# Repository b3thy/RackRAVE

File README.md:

PCB & RaspberryPi image  
for RACKRAVE  
paper(Japanese):  
https://data.jssa.info/paper/2024v16n01/53_5.Kumon.pdf  
Modular synthesizer using realtime audio variational autoencoder  
RAVE:  
https://github.com/acids-ircam/RAVE

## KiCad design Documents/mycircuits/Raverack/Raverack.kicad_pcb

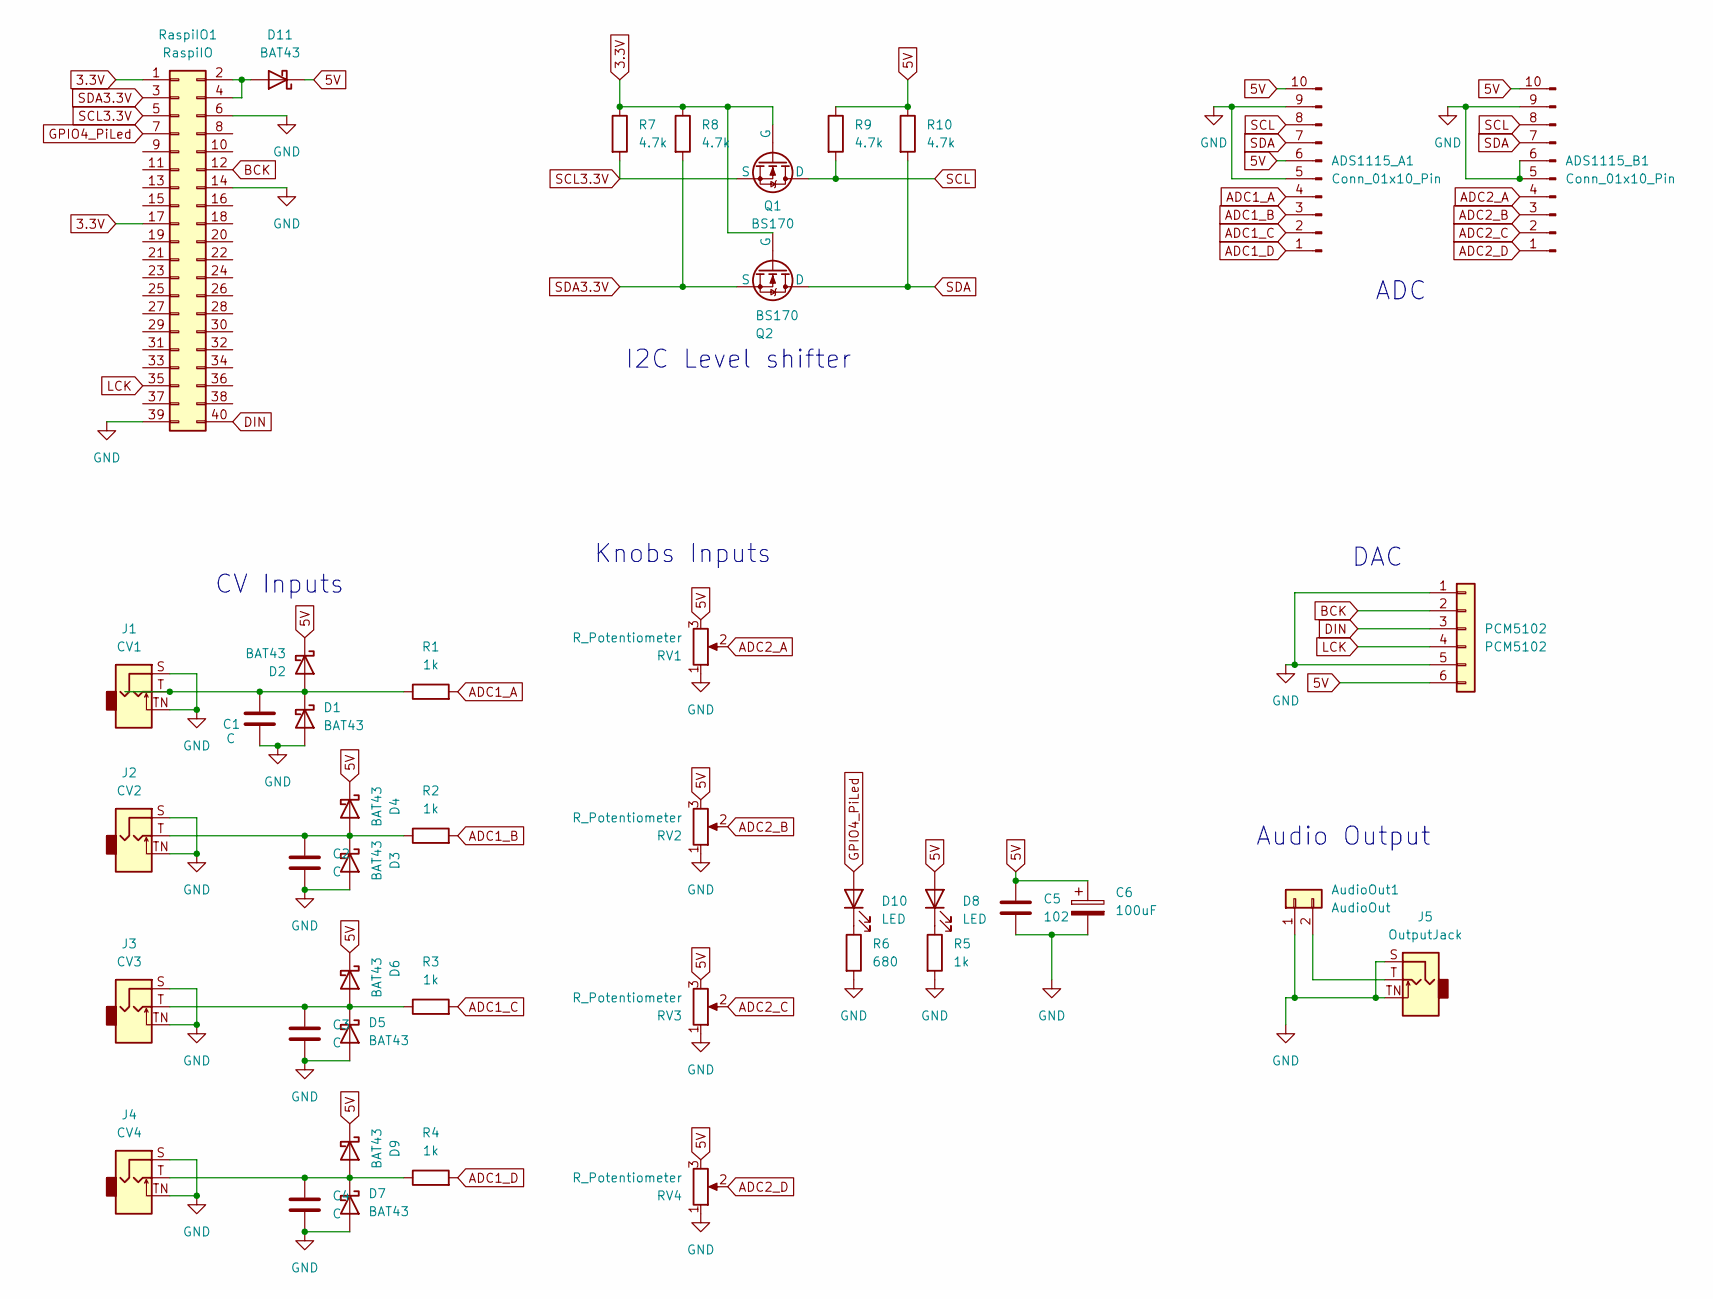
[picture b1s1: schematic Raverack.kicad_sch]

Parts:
ADS1115_A1, ADS1115_B1: Conn_01x10_Pin; PinHeader_1x10_P2.54mm_Vertical
AudioOut1: AudioOut; PinHeader_1x02_P2.54mm_Vertical
C1, C2, C3, C4: C; C_Disc_D3.8mm_W2.6mm_P2.50mm
C5: 102; C_Disc_D3.8mm_W2.6mm_P2.50mm
C6: 100uF; CP_Radial_D5.0mm_P2.50mm
D1, D2, D3, D4, D5, D6, D7, D9, D11: BAT43; D_DO-35_SOD27_P7.62mm_Horizontal
D8, D10: LED; LED_D3.0mm
J1: CV1; Jack_3.5mm_QingPu_WQP-PJ398SM_Vertical_CircularHoles
J2: CV2; Jack_3.5mm_QingPu_WQP-PJ398SM_Vertical_CircularHoles
J3: CV3; Jack_3.5mm_QingPu_WQP-PJ398SM_Vertical_CircularHoles
J4: CV4; Jack_3.5mm_QingPu_WQP-PJ398SM_Vertical_CircularHoles
J5: OutputJack; Jack_3.5mm_QingPu_WQP-PJ398SM_Vertical_CircularHoles
PCM5102: PCM5102; PinHeader_1x06_P2.54mm_Vertical
Q1, Q2: BS170; TO-92_Inline_Wide
R1, R2, R3, R4, R5: 1k; R_Axial_DIN0204_L3.6mm_D1.6mm_P5.08mm_Horizontal
R6: 680; R_Axial_DIN0204_L3.6mm_D1.6mm_P5.08mm_Horizontal
R7, R8, R9, R10: 4.7k; R_Axial_DIN0204_L3.6mm_D1.6mm_P5.08mm_Horizontal
RV1, RV2, RV3, RV4: R_Potentiometer; Potentiometer_Alps_RK09K_Single_Vertical
RaspiIO1: RaspiIO; PinHeader_2x20_P2.54mm_Vertical

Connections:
3.3V: Q1.2 (G), Q2.2 (G), R7.1, R8.1, RaspiIO1.1, RaspiIO1.17
5V: ADS1115_A1.6, ADS1115_A1.10, ADS1115_B1.10, C5.1, C6.1, D2.1 (K), D4.1 (K), D6.1 (K), D8.2 (A), D9.1 (K), D11.1 (K), PCM5102.6, R9.1, R10.1, RV1.3, RV2.3, RV3.3, RV4.3
ADC1_A: ADS1115_A1.4, R1.2
ADC1_B: ADS1115_A1.3, R2.2
ADC1_C: ADS1115_A1.2, R3.2
ADC1_D: ADS1115_A1.1, R4.2
ADC2_A: ADS1115_B1.4, RV1.2
ADC2_B: ADS1115_B1.3, RV2.2
ADC2_C: ADS1115_B1.2, RV3.2
ADC2_D: ADS1115_B1.1, RV4.2
BCK: PCM5102.2, RaspiIO1.12
DIN: PCM5102.3, RaspiIO1.40
GND: ADS1115_A1.5, ADS1115_A1.9, ADS1115_B1.5, ADS1115_B1.6, ADS1115_B1.9, AudioOut1.1, C1.2, C2.2, C3.2, C4.2, C5.2, C6.2, D1.2 (A), D3.2 (A), D5.2 (A), D7.2 (A), J1.S, J1.TN, J2.S, J2.TN, J3.S, J3.TN, J4.S, J4.TN, J5.S, J5.TN, PCM5102.1, PCM5102.5, R5.2, R6.2, RV1.1, RV2.1, RV3.1, RV4.1, RaspiIO1.6, RaspiIO1.14, RaspiIO1.39
GPIO4_PiLed: D10.2 (A), RaspiIO1.7
LCK: PCM5102.4, RaspiIO1.35
unnamed: AudioOut1.2, J5.T
unnamed: C1.1, D1.1 (K), D2.2 (A), J1.T, R1.1
unnamed: C2.1, D3.1 (K), D4.2 (A), J2.T, R2.1
unnamed: C3.1, D5.1 (K), D6.2 (A), J3.T, R3.1
unnamed: C4.1, D7.1 (K), D9.2 (A), J4.T, R4.1
unnamed: D8.1 (K), R5.1
unnamed: D10.1 (K), R6.1
unnamed: D11.2 (A), RaspiIO1.2, RaspiIO1.4
SCL: ADS1115_A1.8, ADS1115_B1.8, Q1.1 (D), R9.2
SCL3.3V: Q1.3 (S), R7.2, RaspiIO1.5
SDA: ADS1115_A1.7, ADS1115_B1.7, Q2.1 (D), R10.2
SDA3.3V: Q2.3 (S), R8.2, RaspiIO1.3

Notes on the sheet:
I2C Level shifter
Knobs Inputs
CV Inputs
ADC
Audio Output
DAC

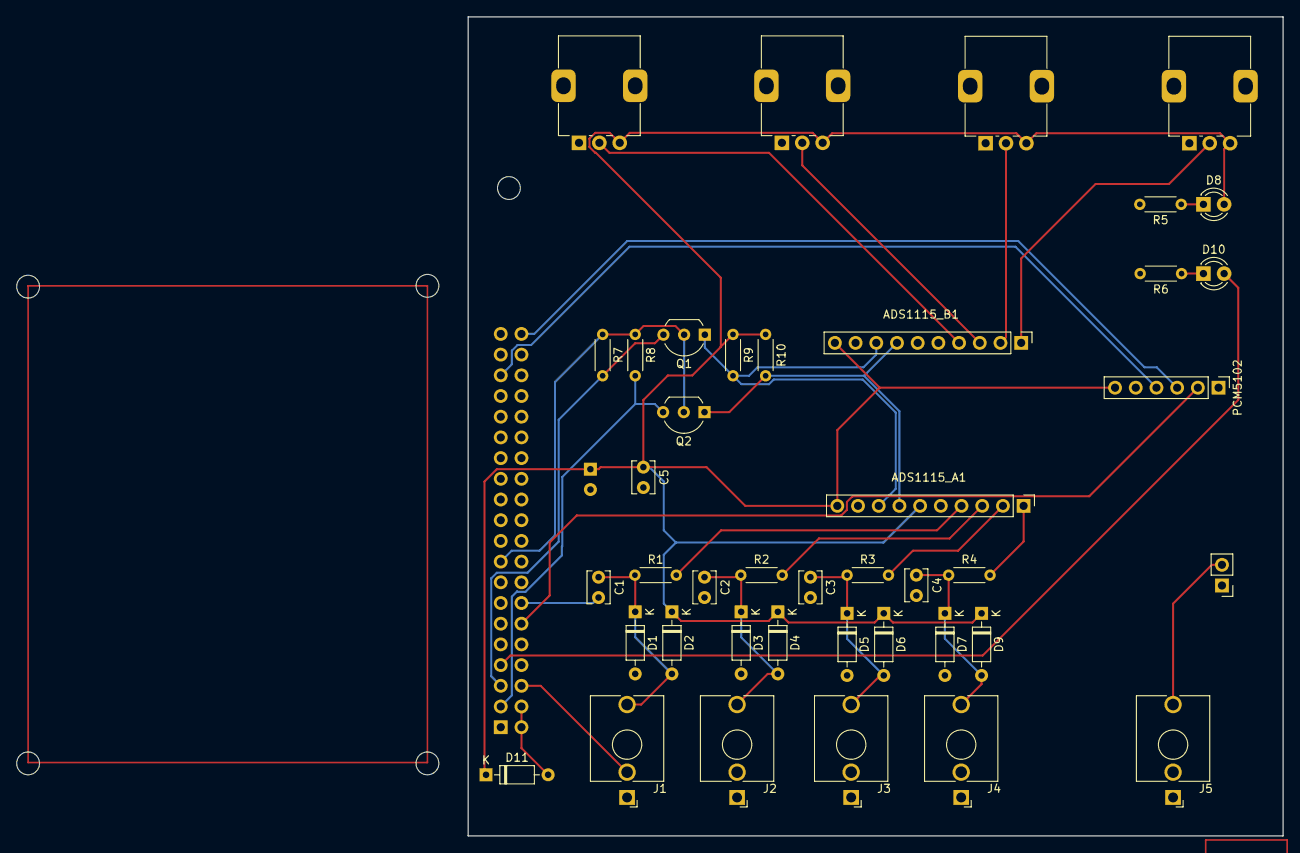
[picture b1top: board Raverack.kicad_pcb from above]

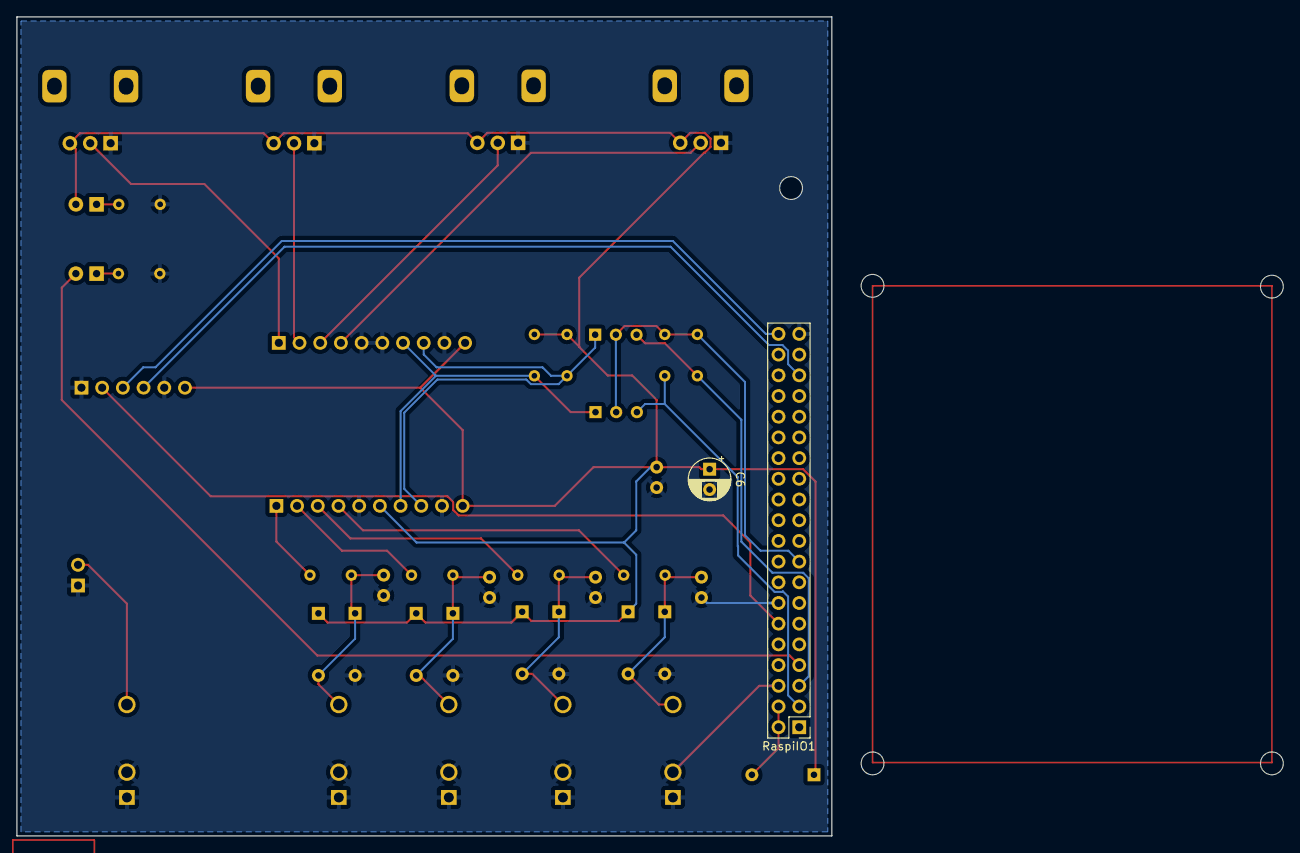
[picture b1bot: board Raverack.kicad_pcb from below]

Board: 2 copper layers, 155.4 x 100.5 mm, 43 parts (2 on the bottom side), 27 nets.

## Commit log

2024-11-05 Add specific folder
2024-11-05 Create LICENSE
